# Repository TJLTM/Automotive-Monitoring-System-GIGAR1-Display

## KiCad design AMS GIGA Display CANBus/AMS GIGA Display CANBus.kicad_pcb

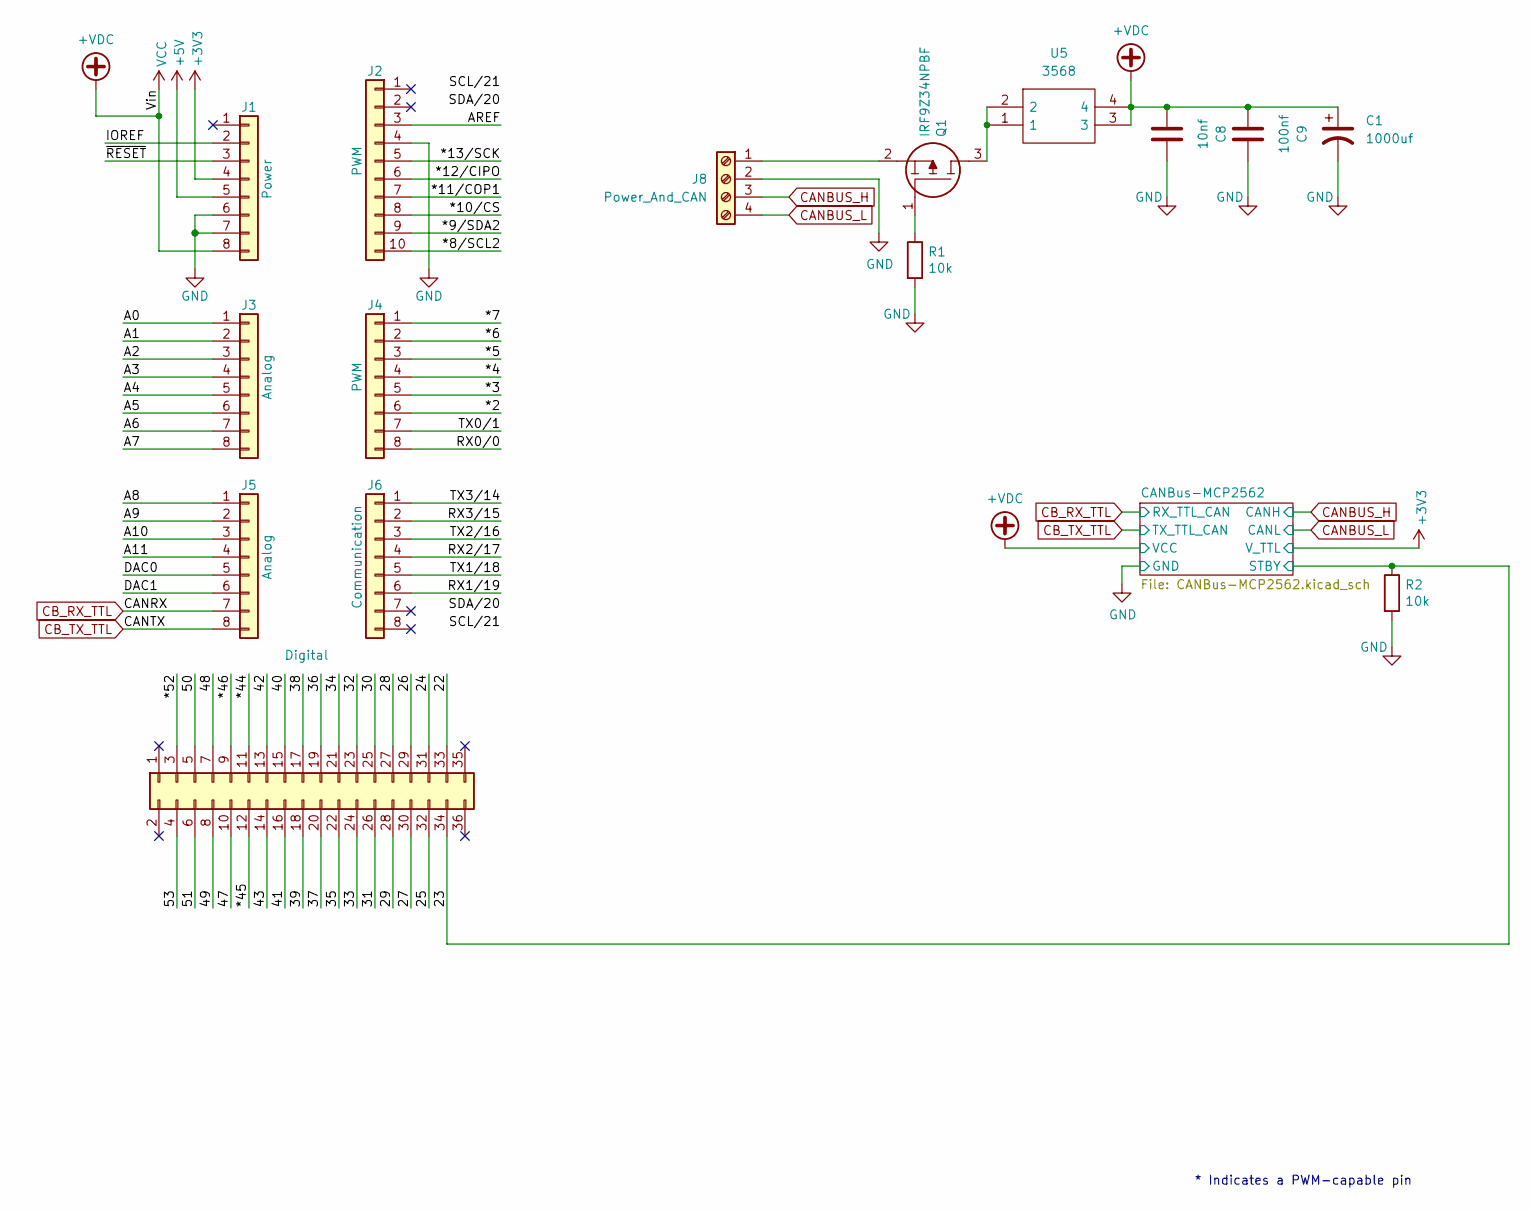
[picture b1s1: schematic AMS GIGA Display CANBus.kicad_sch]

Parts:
C1: 1000uf; CP_Radial_D10.0mm_P5.00mm
C8: 10nf; C_1206_3216Metric_Pad1.33x1.80mm_HandSolder
C9: 100nf; C_1206_3216Metric_Pad1.33x1.80mm_HandSolder
J1: Power; PinSocket_1x08_P2.54mm_Vertical
J2: PWM; PinSocket_1x10_P2.54mm_Vertical
J3, J5: Analog; PinSocket_1x08_P2.54mm_Vertical
J4: PWM; PinSocket_1x08_P2.54mm_Vertical
J6: Communication; PinSocket_1x08_P2.54mm_Vertical
J7: Digital; PinSocket_2x18_P2.54mm_Vertical
J8: Power_And_CAN; TerminalBlock_Phoenix_MPT-0,5-4-2.54_1x04_P2.54mm_Horizontal
Q1: IRF9Z34NPBF; TO254P469X1042X1967-3P; Mouser Part Number 942-IRF9Z34NPBF
R1, R2: 10k; R_1206_3216Metric_Pad1.30x1.75mm_HandSolder
U5: 3568; Mouser Part Number 534-3568

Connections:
+3V3: J1.4; also elsewhere on the board
+5V: J1.5
+VDC: C1.1, C8.1, C9.1, J1.8, U5.3, U5.4; also elsewhere on the board
/22: J7.33
/23: J7.34, R2.1; also elsewhere on the board
/24: J7.31
/25: J7.32
/26: J7.29
/27: J7.30
/28: J7.27
/29: J7.28
/30: J7.25
/31: J7.26
/32: J7.23
/33: J7.24
/34: J7.21
/35: J7.22
/36: J7.19
/37: J7.20
/38: J7.17
/39: J7.18
/40: J7.15
/41: J7.16
/42: J7.13
/43: J7.14
/47: J7.10
/48: J7.7
/49: J7.8
/50: J7.5
/51: J7.6
/53: J7.4
/*2: J4.6
/*3: J4.5
/*4: J4.4
/*5: J4.3
/*6: J4.2
/*7: J4.1
/*8/SCL2: J2.10
/*9/SDA2: J2.9
/*10/CS: J2.8
/*11/COP1: J2.7
/*12/CIPO: J2.6
/*13/SCK: J2.5
/*44: J7.11
/*45: J7.12
/*46: J7.9
/*52: J7.3
/A0: J3.1
/A1: J3.2
/A2: J3.3
/A3: J3.4
/A4: J3.5
/A5: J3.6
/A6: J3.7
/A7: J3.8
/A8: J5.1
/A9: J5.2
/A10: J5.3
/A11: J5.4
/AREF: J2.3
/DAC0: J5.5
/DAC1: J5.6
/IOREF: J1.2
/RX0/0: J4.8
/RX1/19: J6.6
/RX2/17: J6.4
/RX3/15: J6.2
/TX0/1: J4.7
/TX1/18: J6.5
/TX2/16: J6.3
/TX3/14: J6.1
/~RESET: J1.3
CANBUS_H: J8.3; also elsewhere on the board
CANBUS_L: J8.4; also elsewhere on the board
CB_RX_TTL: J5.7; also elsewhere on the board
CB_TX_TTL: J5.8; also elsewhere on the board
GND: C1.2, C8.2, C9.2, J1.6, J1.7, J2.4, J8.2, R1.2, R2.2; also elsewhere on the board
unnamed: J8.1, Q1.2
unnamed: Q1.1, R1.1
unnamed: Q1.3, U5.1, U5.2

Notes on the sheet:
* Indicates a PWM-capable pin

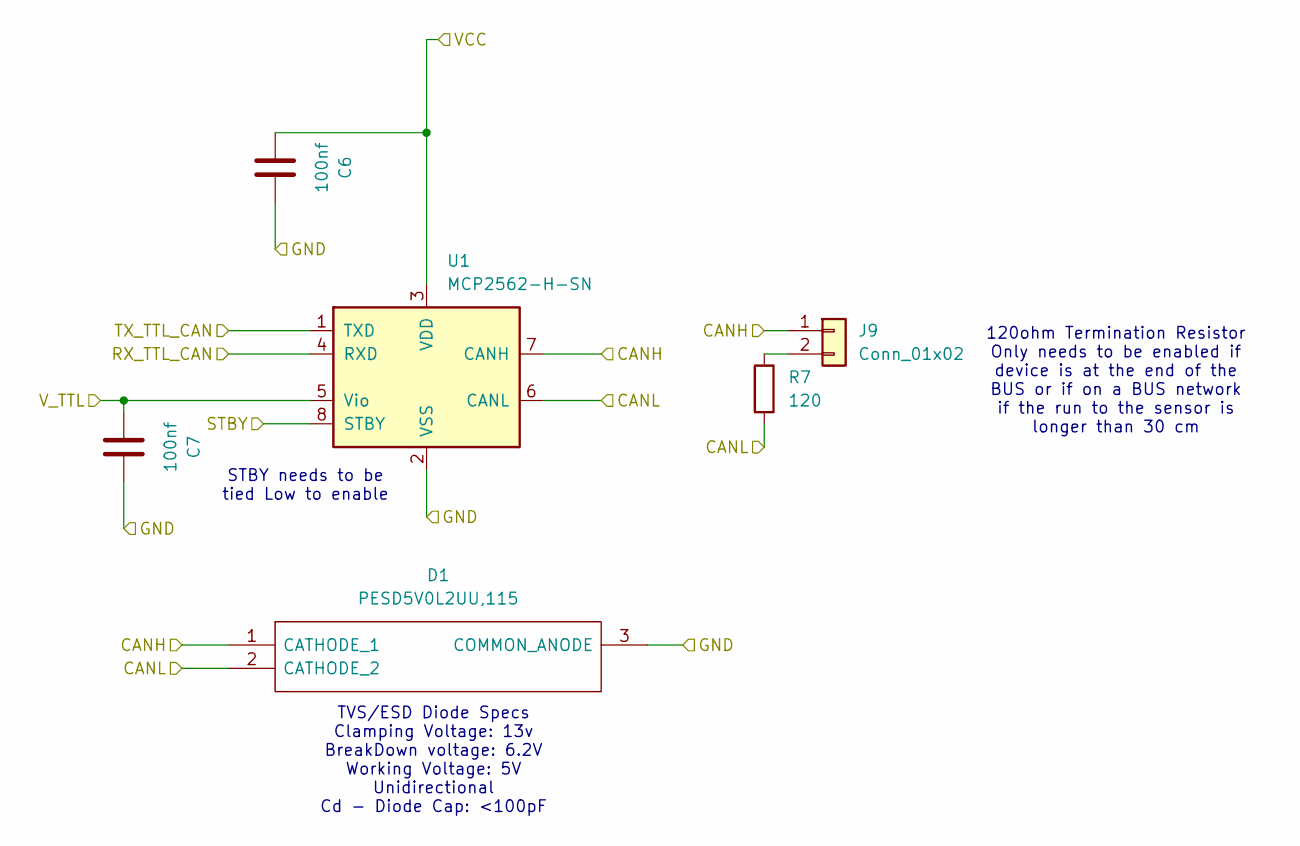
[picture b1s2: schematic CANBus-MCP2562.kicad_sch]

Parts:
C6, C7: 100nf; C_1206_3216Metric_Pad1.33x1.80mm_HandSolder
D1: PESD5V0L2UU,115; SOT65P210X110-3N; Mouser Part Number 771-PESD5V0L2UU115
J9: Conn_01x02; PinHeader_1x02_P2.54mm_Vertical
R7: 120; R_Axial_DIN0207_L6.3mm_D2.5mm_P2.54mm_Vertical
U1: MCP2562-H-SN; SOIC-8_3.9x4.9mm_P1.27mm

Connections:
+3V3: C7.1, U1.5 (Vio); also elsewhere on the board
+VDC: C6.1, U1.3 (VDD); also elsewhere on the board
/23: U1.8 (STBY); also elsewhere on the board
CANBUS_H: D1.1 (CATHODE_1), J9.1, U1.7 (CANH); also elsewhere on the board
CANBUS_L: D1.2 (CATHODE_2), R7.2, U1.6 (CANL); also elsewhere on the board
CB_RX_TTL: U1.4 (RXD); also elsewhere on the board
CB_TX_TTL: U1.1 (TXD); also elsewhere on the board
GND: C6.2, C7.2, D1.3 (COMMON_ANODE), U1.2 (VSS); also elsewhere on the board
unnamed: J9.2, R7.1

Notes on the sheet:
120ohm Termination Resistor Only needs to be enabled if device is at the end of the BUS or if on a BUS network if the run to the sensor is longer than 30 cm
TVS/ESD Diode Specs Clamping Voltage: 13v BreakDown voltage: 6.2V Working Voltage: 5V Unidirectional Cd - Diode Cap: <100pF
STBY needs to be tied Low to enable

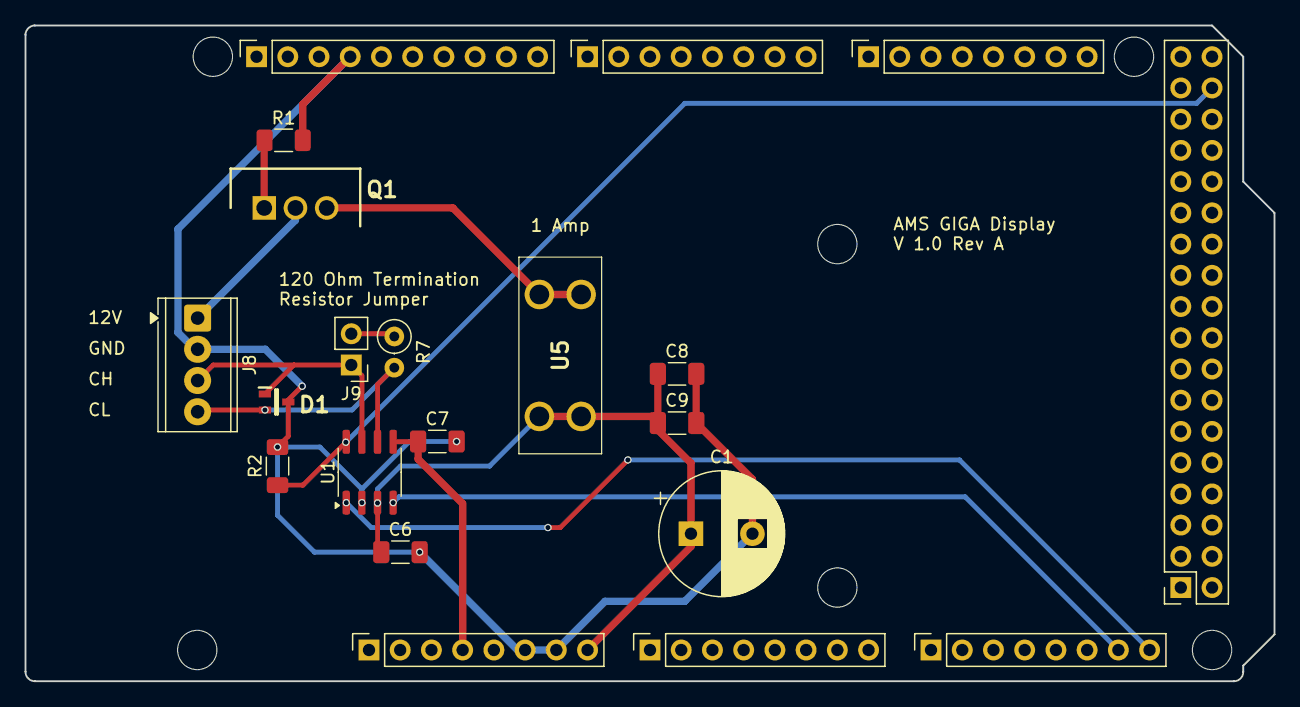
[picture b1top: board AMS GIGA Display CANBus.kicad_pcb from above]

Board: 2 copper layers, 101.6 x 53.3 mm, 27 parts (0 on the bottom side), 12 nets.

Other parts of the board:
MH1, MH2, MH3, MH4, MH5, MH6: MountingHole_3.2mm

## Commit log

2025-01-27 initial blank project
2025-03-02 initial HW commit
2025-10-31 removing
2025-10-31 adding the quick project i made with the new CANbus chip
2025-11-11 added some silkscreen labeling that i forgot to add before fab oh well.
2025-11-13 just a starting point for this.
